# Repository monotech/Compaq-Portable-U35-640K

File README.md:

# Compaq Portable RAM Decoder PROM (U35)
SPLD-based replacement of RAM decoder PROM in Compaq Portable, allowing either 256K or 640K RAM on the system board.

This goes into socket U35 on the original Compaq Portable motherboard.

This isn't for later model Compaq Portable motherboards, which use jumpers instead and don't need a PROM replaced to upgrade onboard RAM.

If you'd like to have 256K RAM onboard and you don't own a 256K U35 (PN 100340-001 (some PROMs only have the PROM model enscribed)), you can install this and close the jumper to put it into 256K mode. Then ensure the two socketed DRAM banks contain 64Kx1 ICs (256Kx1 ICs should work just fine too).

If you'd like to have 640K RAM onboard and you don't own a 640K U35 (PN 101257-001 (some PROMs only have the PROM model enscribed)), you can install this and remove the jumper to put it into 640K mode. Then ensure the two socketed DRAM banks contain 256Kx1 ICs.

# Why?
Compaq officially supported three different RAM configs in the Compaq Portable: 256K, 448K, and 640K. Changing the config meant installing different amounts of 64Kx1 and 256Kx1 DRAM ICs, as well as swapping the 82S123-type bipolar PROM (U35) with one for that specific config. Compaq sold these PROMs, and I don't think they've all been dumped. At the time of designing this, I only had the 256K PROM, but after dumping it, it wasn't difficult to work out how the 640K one would work.

This is useful because it can save you an ISA slot, since you no longer need to use one up to get 640K RAM.

I did experiment trying to install a third bank of 256K, and using some as UMB, but it seemed to 'almost' work, but was unstable. It was a few years ago so I don't remember the exact details.

If this page is still up, then I should have stock if you'd just like to buy one instead - I have the DRAM ICs too: https://monotech.fwscart.com/Compaq_Portable_640K_U35_RAM_Decoder_PROM/p6083514_19805777.aspx

# License
Creative Commons CC BY-SA 4.0: https://creativecommons.org/licenses/by-sa/4.0/.

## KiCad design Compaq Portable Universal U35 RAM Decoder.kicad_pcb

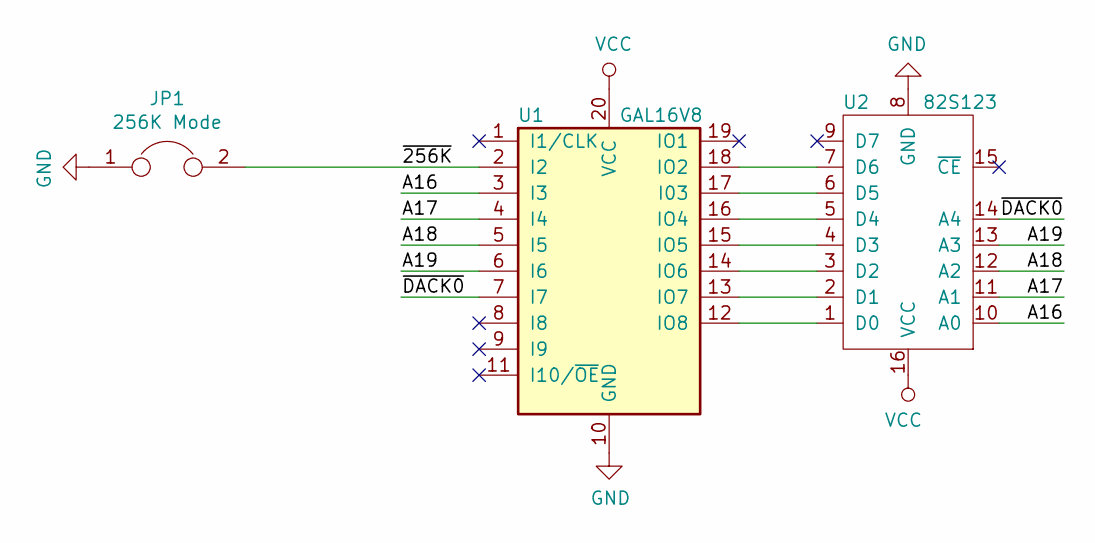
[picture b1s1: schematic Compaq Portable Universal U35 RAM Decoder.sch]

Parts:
JP1: 256K Mode; PinHeader_1x02_P2.54mm_Horizontal
U1: GAL16V8; DIP-20_W7.62mm_Socket
U2: 82S123; DIP-16_W7.62mm_Socket

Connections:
/A16: U1.3 (I3), U2.10 (A0)
/A17: U1.4 (I4), U2.11 (A1)
/A18: U1.5 (I5), U2.12 (A2)
/A19: U1.6 (I6), U2.13 (A3)
/~256K: JP1.2, U1.2 (I2)
/~DACK0: U1.7 (I7), U2.14 (A4)
GND: JP1.1, U1.10 (GND), U2.8 (GND)
unnamed: U1.12 (IO8), U2.1 (D0)
unnamed: U1.13 (IO7), U2.2 (D1)
unnamed: U1.14 (IO6), U2.3 (D2)
unnamed: U1.15 (IO5), U2.4 (D3)
unnamed: U1.16 (IO4), U2.5 (D4)
unnamed: U1.17 (I03), U2.6 (D5)
unnamed: U1.18 (IO2), U2.7 (D6)
VCC: U1.20 (VCC), U2.16 (VCC)

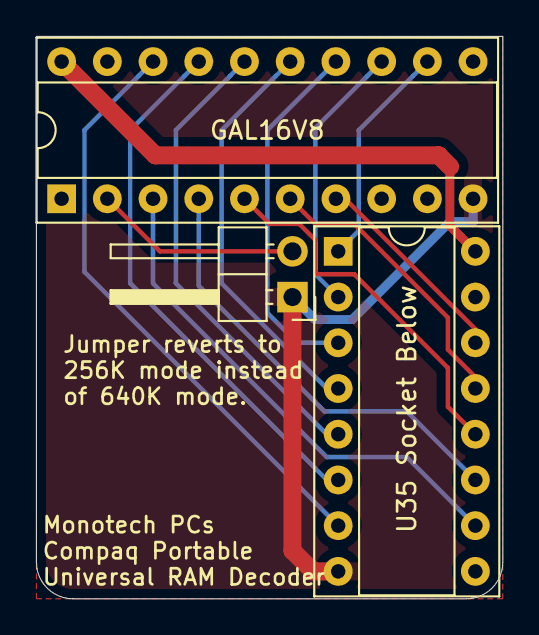
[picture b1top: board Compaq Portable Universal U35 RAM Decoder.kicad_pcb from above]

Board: 2 copper layers, 25.9 x 31.2 mm, 3 parts (0 on the bottom side), 15 nets.
